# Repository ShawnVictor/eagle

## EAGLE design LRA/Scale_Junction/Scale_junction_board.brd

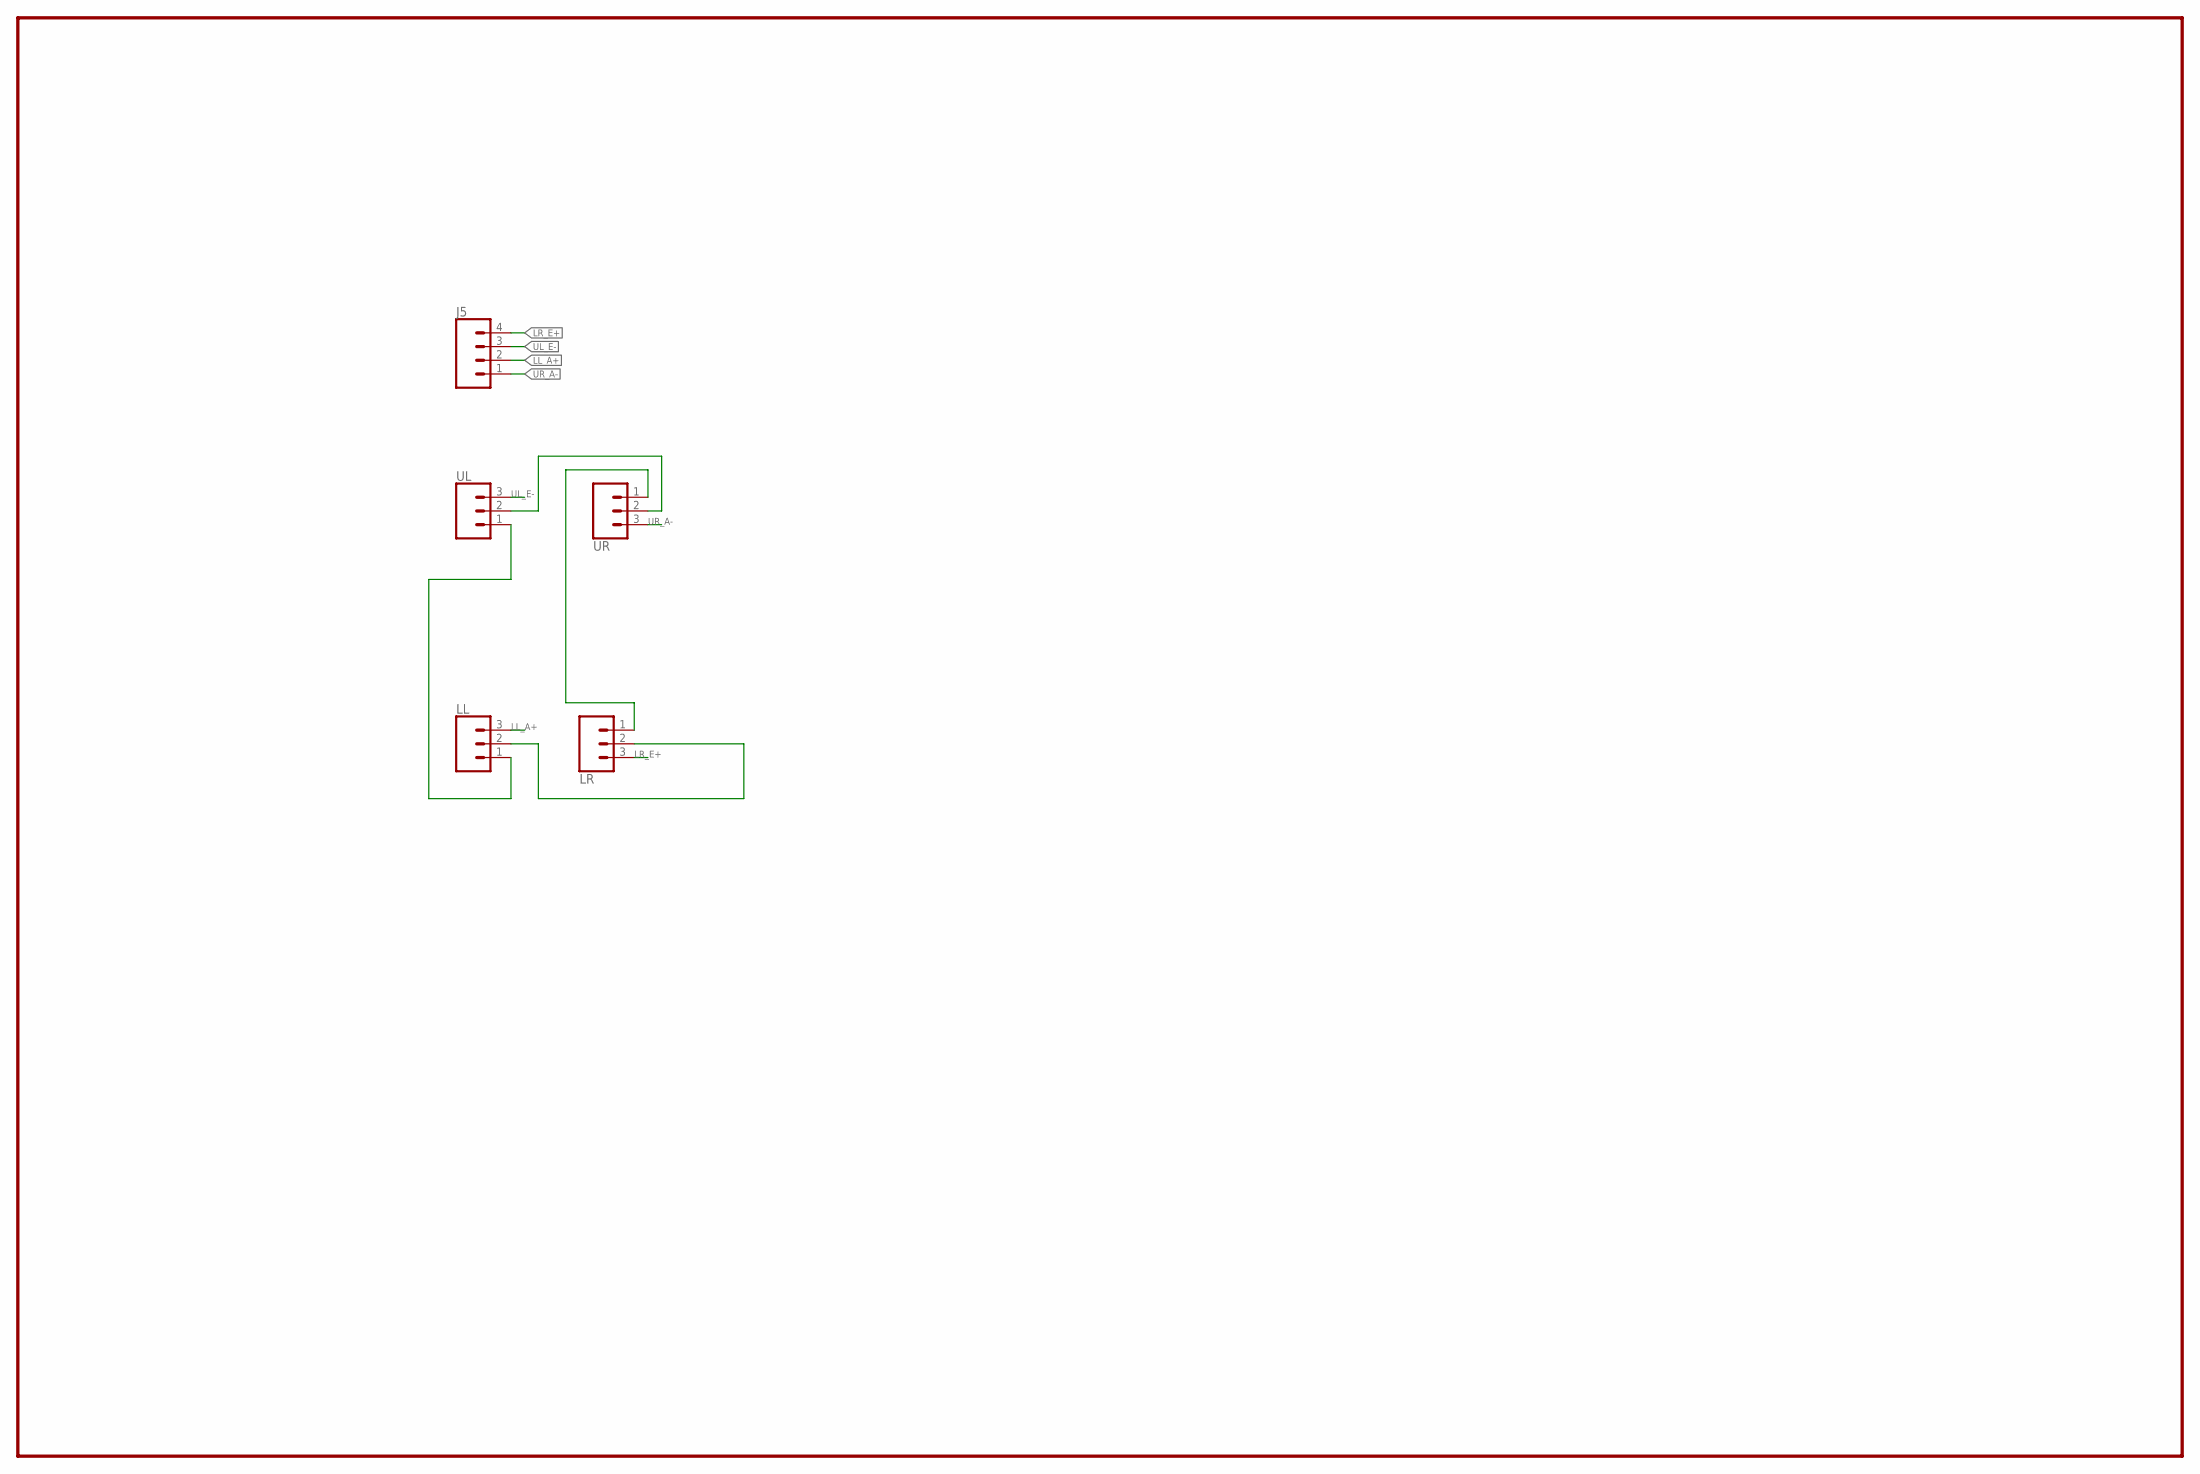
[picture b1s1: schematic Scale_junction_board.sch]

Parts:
J5: CONN_04LONGPADS; 1X04_LONGPADS
LL: CONN_03LONGPADS; 1X03_LONGPADS
LR: CONN_03LONGPADS; 1X03_LONGPADS
UL: CONN_03LONGPADS; 1X03_LONGPADS
UR: CONN_03LONGPADS; 1X03_LONGPADS

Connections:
LL_A+: J5.2, LL.3
LR_E+: J5.4, LR.3
unnamed: LL.1, UL.1
unnamed: LR.1, UR.1
unnamed: UL.2, UR.2
unnamed: LL.2, LR.2
UL_E-: J5.3, UL.3
UR_A-: J5.1, UR.3

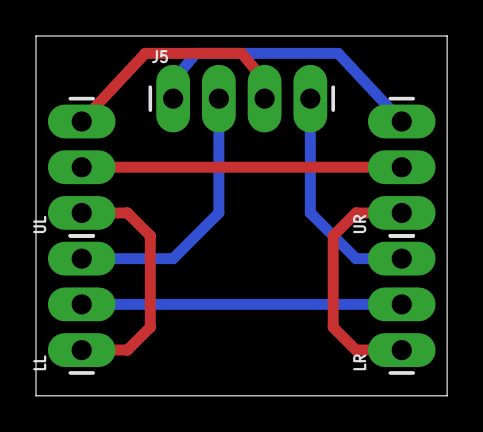
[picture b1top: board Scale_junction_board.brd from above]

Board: 2 copper layers, 22.8 x 20.0 mm, 5 parts (0 on the bottom side), 8 nets.

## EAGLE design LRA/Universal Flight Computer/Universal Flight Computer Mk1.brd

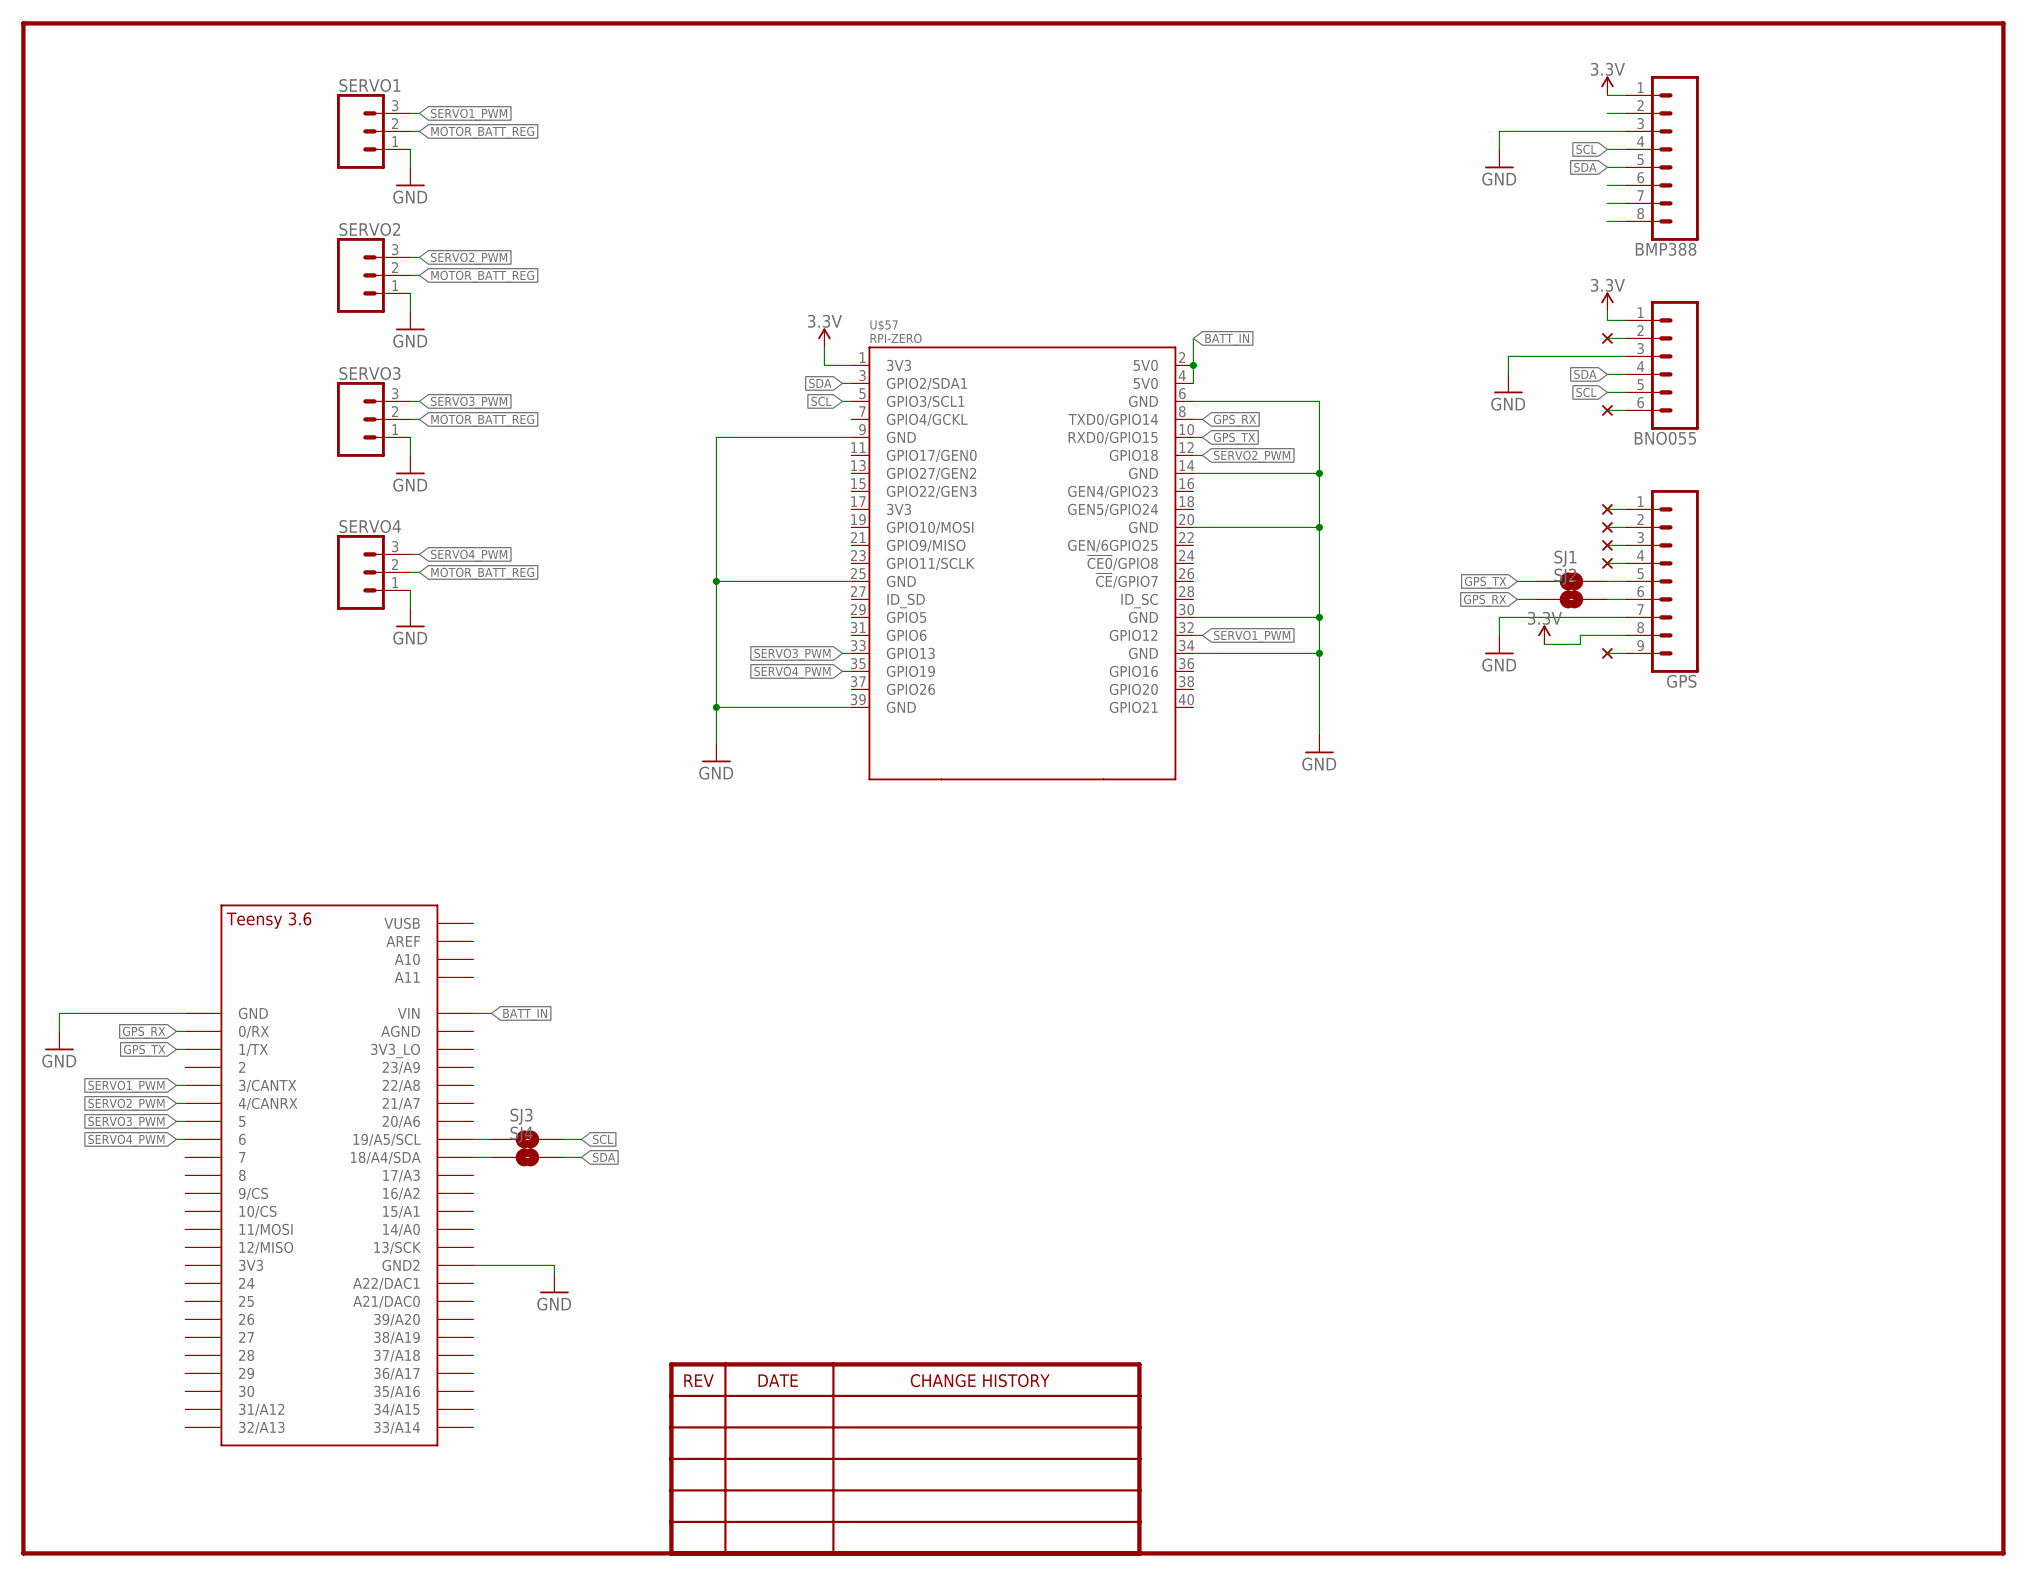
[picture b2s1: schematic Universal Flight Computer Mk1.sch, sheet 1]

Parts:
BMP388: CONN_08"; 1X08
BNO055: CONN_06SILK_FEMALE_PTH; 1X06
GPS: CONN_09; 1X09
SERVO1, SERVO2, SERVO3, SERVO4: CONN_03; 1X03
SJ1, SJ2, SJ3, SJ4: SOLDERJUMPERNO; SJ_2S-NO
U$5, U$6, U$7, U$8, U$9, U$10, U$11: NC
U$12: TEENSY_3.5/3.6_BASIC
U$57: RPI-ZERO; RASPBERRYPI_BASTELSTUBE_V13_RASPI_BOARD_B+_FULL

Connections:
3.3V: BMP388.1, BNO055.1, GPS.8, U$57.1 (3V3)
BATT_IN: U$12.VIN, U$57.2 (5V0), U$57.4 (5V0); also elsewhere on the board
BMP_CS: BMP388.7
BMP_INT: BMP388.8
BMP_SDI: BMP388.6
GND: BMP388.3, BNO055.3, GPS.7, SERVO1.1, SERVO2.1, SERVO3.1, SERVO4.1, U$12.GND, U$12.GND2, U$57.6 (GND), U$57.9 (GND), U$57.14 (GND), U$57.20 (GND), U$57.25 (GND), U$57.30 (GND), U$57.34 (GND), U$57.39 (GND); also elsewhere on the board
GPS_RX: GPS.6, SJ2.1, SJ2.2, U$12.0/RX, U$57.8 (TXD0/GPIO14)
GPS_TX: GPS.5, SJ1.1, SJ1.2, U$12.1/TX, U$57.10 (RXD0/GPIO15)
MOTOR_BATT_REG: SERVO1.2, SERVO2.2, SERVO3.2, SERVO4.2; also elsewhere on the board
unnamed: SJ3.1, U$12.19/A5/SCL
unnamed: SJ4.1, U$12.18/A4/SDA
SCL: BMP388.4, BNO055.5, SJ3.2, U$57.5 (GPIO3/SCL1)
SDA: BMP388.5, BNO055.4, SJ4.2, U$57.3 (GPIO2/SDA1)
SERVO1_PWM: SERVO1.3, U$12.3/CANTX, U$57.32 (GPIO12)
SERVO2_PWM: SERVO2.3, U$12.4/CANRX, U$57.12 (GPIO18)
SERVO3_PWM: SERVO3.3, U$12.5, U$57.33 (GPIO13)
SERVO4_PWM: SERVO4.3, U$12.6, U$57.35 (GPIO19)

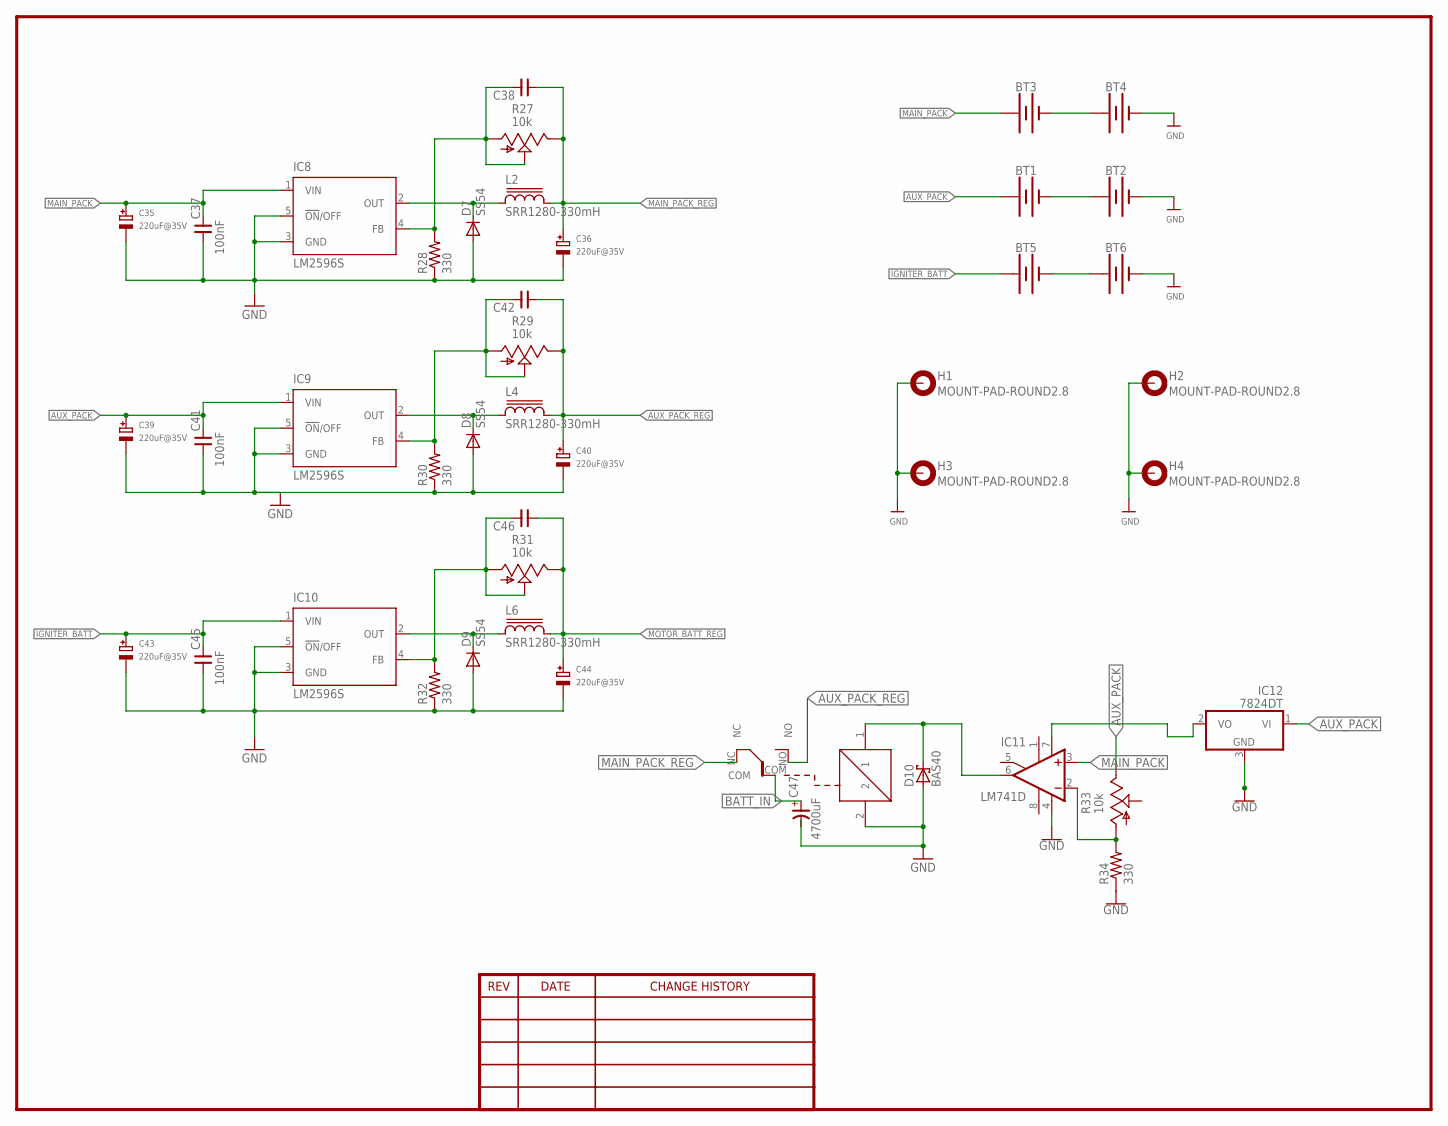
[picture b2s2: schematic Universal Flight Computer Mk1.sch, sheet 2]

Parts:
BT1, BT2, BT3, BT4, BT5, BT6: BATTERY-18650; BATTERY_18650-HOLDER
C35, C36, C39, C40, C43, C44: 220uF@35V; PANASONIC_D
C37, C41, C45: 100nF; 0603
C38, C42, C46: CNP-0603; 0603
C47: 4700uF; E-025X065
D7, D8, D9: SS54; DO214AB
D10: BAS40; SOT23
H1, H2, H3, H4: MOUNT-PAD-ROUND2.8; 2,8-PAD
IC8, IC9, IC10: LM2596S; TO263-5
IC11: LM741D; SO08
IC12: 7824DT; TO252
L2, L4, L6: SRR1280-330mH; SRR1280
R27, R29, R31, R33: 10k; S64W
R28, R30, R32, R34: 330; R0603
U$54: RW-SH

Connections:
AUX_PACK: BT1.PWR@1 (+), C39.+, C41.2, IC9.1 (VIN), IC12.1 (VI), R33.E
AUX_PACK_REG: C40.+, C42.1, L4.2, R29.E, U$54.NO
BATT_IN: C47.+, D10.3 (C), IC11.6 (OUT), U$54.1, U$54.COM; also elsewhere on the board
GND: BT2.GND@1 (-), BT4.GND@1 (-), BT6.GND@1 (-), C39.-, C40.-, C41.1, C43.-, C44.-, C45.1, D8.A, D9.A, D10.1 (A), H1.B2,8, H2.B2,8, H3.B2,8, H4.B2,8, IC9.3 (GND), IC9.5 (!ON!/OFF), IC10.3 (GND), IC10.5 (!ON!/OFF), IC11.4 (V-), IC12.3 (GND), R30.1, R32.1, R34.1, U$54.2; also elsewhere on the board
IGNITER_BATT: BT5.PWR@1 (+), C43.+, C45.2, IC10.1 (VIN)
MAIN_PACK: BT3.PWR@1 (+), C35.+, C35.-, C36.-, C37.1, C37.2, D7.A, IC8.1 (VIN), IC8.3 (GND), IC8.5 (!ON!/OFF), IC11.3 (+IN), R28.1
MAIN_PACK_REG: C36.+, C38.1, L2.2, R27.E, U$54.NC
MOTOR_BATT_REG: C44.+, C46.1, L6.2, R31.E; also elsewhere on the board
unnamed: BT3.GND@1 (-), BT4.PWR@1 (+)
unnamed: BT1.GND@1 (-), BT2.PWR@1 (+)
unnamed: D7.C, IC8.2 (OUT), L2.1
unnamed: C38.2, IC8.4 (FB), R27.A, R27.S, R28.2
unnamed: D8.C, IC9.2 (OUT), L4.1
unnamed: C42.2, IC9.4 (FB), R29.A, R29.S, R30.2
unnamed: D9.C, IC10.2 (OUT), L6.1
unnamed: C46.2, IC10.4 (FB), R31.A, R31.S, R32.2
unnamed: IC11.2 (-IN), R33.A, R34.2
unnamed: IC11.7 (V+), IC12.2 (VO)
unnamed: BT5.GND@1 (-), BT6.PWR@1 (+)

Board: 4 copper layers, 64 parts (18 on the bottom side), 30 nets, no tracks yet.

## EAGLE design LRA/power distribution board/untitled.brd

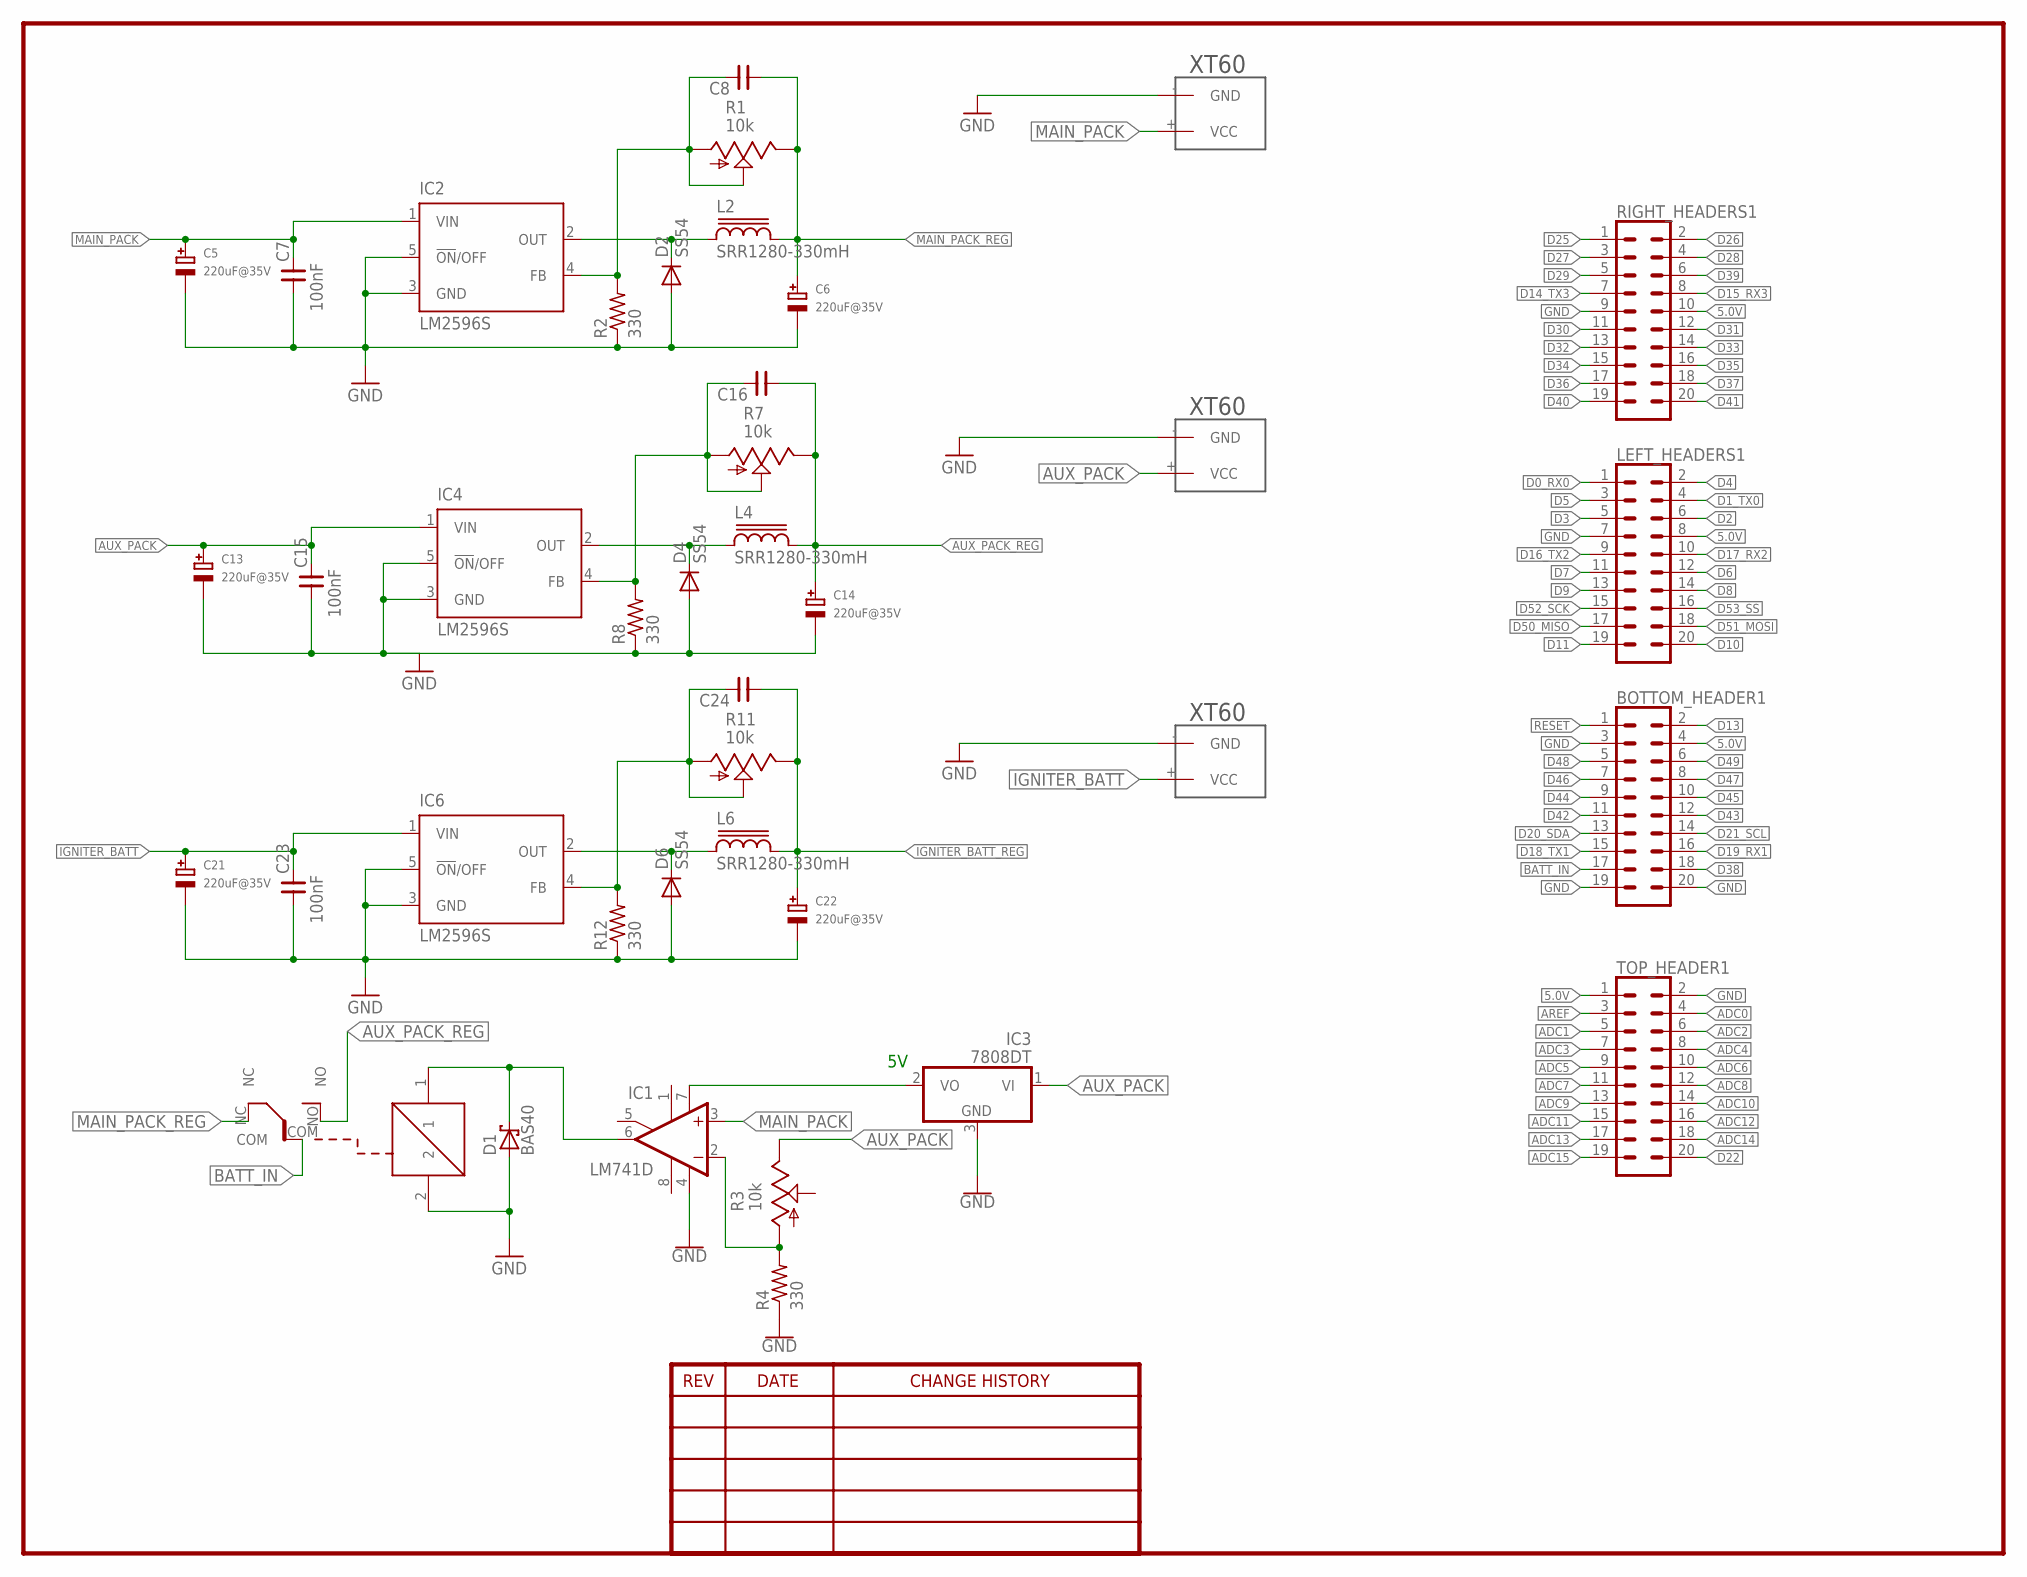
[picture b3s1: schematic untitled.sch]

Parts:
BOTTOM_HEADER1: CONN_10X2; 2X10
C5, C6, C13, C14, C21, C22: 220uF@35V; PANASONIC_D
C7, C15, C23: 100nF; 0603
C8, C16, C24: CNP-0603; 0603
D1: BAS40; SOT23
D2, D4, D6: SS54; DO214AB
IC1: LM741D; SO08
IC2, IC4, IC6: LM2596S; TO263-5
IC3: 7808DT; TO252
L2, L4, L6: SRR1280-330mH; SRR1280
LEFT_HEADERS1: CONN_10X2; 2X10
R1, R3, R7, R11: 10k; S64W
R2, R4, R8, R12: 330; R0603
RIGHT_HEADERS1: CONN_10X2; 2X10
TOP_HEADER1: CONN_10X2; 2X10
U$1, U$2, U$3: XT60
U$9: RW-SH

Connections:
5.0V: BOTTOM_HEADER1.4, LEFT_HEADERS1.8, RIGHT_HEADERS1.10, TOP_HEADER1.1
ADC0: TOP_HEADER1.4
ADC1: TOP_HEADER1.5
ADC2: TOP_HEADER1.6
ADC3: TOP_HEADER1.7
ADC4: TOP_HEADER1.8
ADC5: TOP_HEADER1.9
ADC6: TOP_HEADER1.10
ADC7: TOP_HEADER1.11
ADC8: TOP_HEADER1.12
ADC9: TOP_HEADER1.13
ADC10: TOP_HEADER1.14
ADC11: TOP_HEADER1.15
ADC12: TOP_HEADER1.16
ADC13: TOP_HEADER1.17
ADC14: TOP_HEADER1.18
ADC15: TOP_HEADER1.19
AREF: TOP_HEADER1.3
AUX_PACK: C13.+, C15.2, IC3.1 (VI), IC4.1 (VIN), R3.E, U$2.+ (VCC)
AUX_PACK_REG: C14.+, C16.1, L4.2, R7.E, U$9.NO
BATT_IN: BOTTOM_HEADER1.17, D1.3 (C), IC1.6 (OUT), U$9.1, U$9.COM
D0_RX0: LEFT_HEADERS1.1
D1_TX0: LEFT_HEADERS1.4
D2: LEFT_HEADERS1.6
D3: LEFT_HEADERS1.5
D4: LEFT_HEADERS1.2
D5: LEFT_HEADERS1.3
D6: LEFT_HEADERS1.12
D7: LEFT_HEADERS1.11
D8: LEFT_HEADERS1.14
D9: LEFT_HEADERS1.13
D10: LEFT_HEADERS1.20
D11: LEFT_HEADERS1.19
D13: BOTTOM_HEADER1.2
D14_TX3: RIGHT_HEADERS1.7
D15_RX3: RIGHT_HEADERS1.8
D16_TX2: LEFT_HEADERS1.9
D17_RX2: LEFT_HEADERS1.10
D18_TX1: BOTTOM_HEADER1.15
D19_RX1: BOTTOM_HEADER1.16
D20_SDA: BOTTOM_HEADER1.13
D21_SCL: BOTTOM_HEADER1.14
D22: TOP_HEADER1.20
D25: RIGHT_HEADERS1.1
D26: RIGHT_HEADERS1.2
D27: RIGHT_HEADERS1.3
D28: RIGHT_HEADERS1.4
D29: RIGHT_HEADERS1.5
D30: RIGHT_HEADERS1.11
D31: RIGHT_HEADERS1.12
D32: RIGHT_HEADERS1.13
D33: RIGHT_HEADERS1.14
D34: RIGHT_HEADERS1.15
D35: RIGHT_HEADERS1.16
D36: RIGHT_HEADERS1.17
D37: RIGHT_HEADERS1.18
D38: BOTTOM_HEADER1.18
D39: RIGHT_HEADERS1.6
D40: RIGHT_HEADERS1.19
D41: RIGHT_HEADERS1.20
D42: BOTTOM_HEADER1.11
D43: BOTTOM_HEADER1.12
D44: BOTTOM_HEADER1.9
D45: BOTTOM_HEADER1.10
D46: BOTTOM_HEADER1.7
D47: BOTTOM_HEADER1.8
D48: BOTTOM_HEADER1.5
D49: BOTTOM_HEADER1.6
D50_MISO: LEFT_HEADERS1.17
D51_MOSI: LEFT_HEADERS1.18
D52_SCK: LEFT_HEADERS1.15
D53_SS: LEFT_HEADERS1.16
GND: BOTTOM_HEADER1.3, BOTTOM_HEADER1.19, BOTTOM_HEADER1.20, C13.-, C14.-, C15.1, C21.-, C22.-, C23.1, D1.1 (A), D4.A, D6.A, IC1.4 (V-), IC3.3 (GND), IC4.3 (GND), IC4.5 (!ON!/OFF), IC6.3 (GND), IC6.5 (!ON!/OFF), LEFT_HEADERS1.7, R4.1, R8.1, R12.1, RIGHT_HEADERS1.9, TOP_HEADER1.2, U$1.- (GND), U$2.- (GND), U$3.- (GND), U$9.2
IGNITER_BATT: C21.+, C23.2, IC6.1 (VIN), U$3.+ (VCC)
IGNITER_BATT_REG: C22.+, C24.1, L6.2, R11.E
MAIN_PACK: C5.+, C5.-, C6.-, C7.1, C7.2, D2.A, IC1.3 (+IN), IC2.1 (VIN), IC2.3 (GND), IC2.5 (!ON!/OFF), R2.1, U$1.+ (VCC)
MAIN_PACK_REG: C6.+, C8.1, L2.2, R1.E, U$9.NC
unnamed: D2.C, IC2.2 (OUT), L2.1
unnamed: C8.2, IC2.4 (FB), R1.A, R1.S, R2.2
unnamed: IC1.2 (-IN), R3.A, R4.2
unnamed: D4.C, IC4.2 (OUT), L4.1
unnamed: C16.2, IC4.4 (FB), R7.A, R7.S, R8.2
unnamed: IC1.7 (V+), IC3.2 (VO)
unnamed: D6.C, IC6.2 (OUT), L6.1
unnamed: C24.2, IC6.4 (FB), R11.A, R11.S, R12.2
RESET: BOTTOM_HEADER1.1

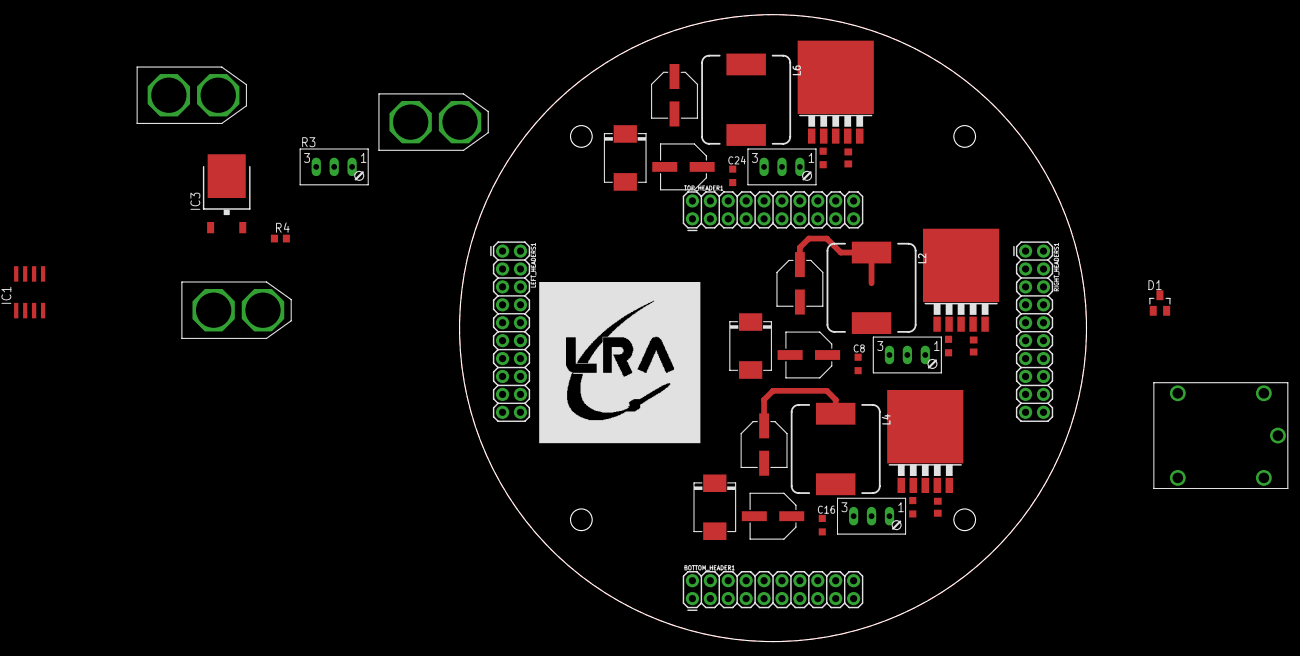
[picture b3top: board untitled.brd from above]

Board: 2 copper layers, 88.9 x 88.9 mm, 40 parts (0 on the bottom side), 17 nets.

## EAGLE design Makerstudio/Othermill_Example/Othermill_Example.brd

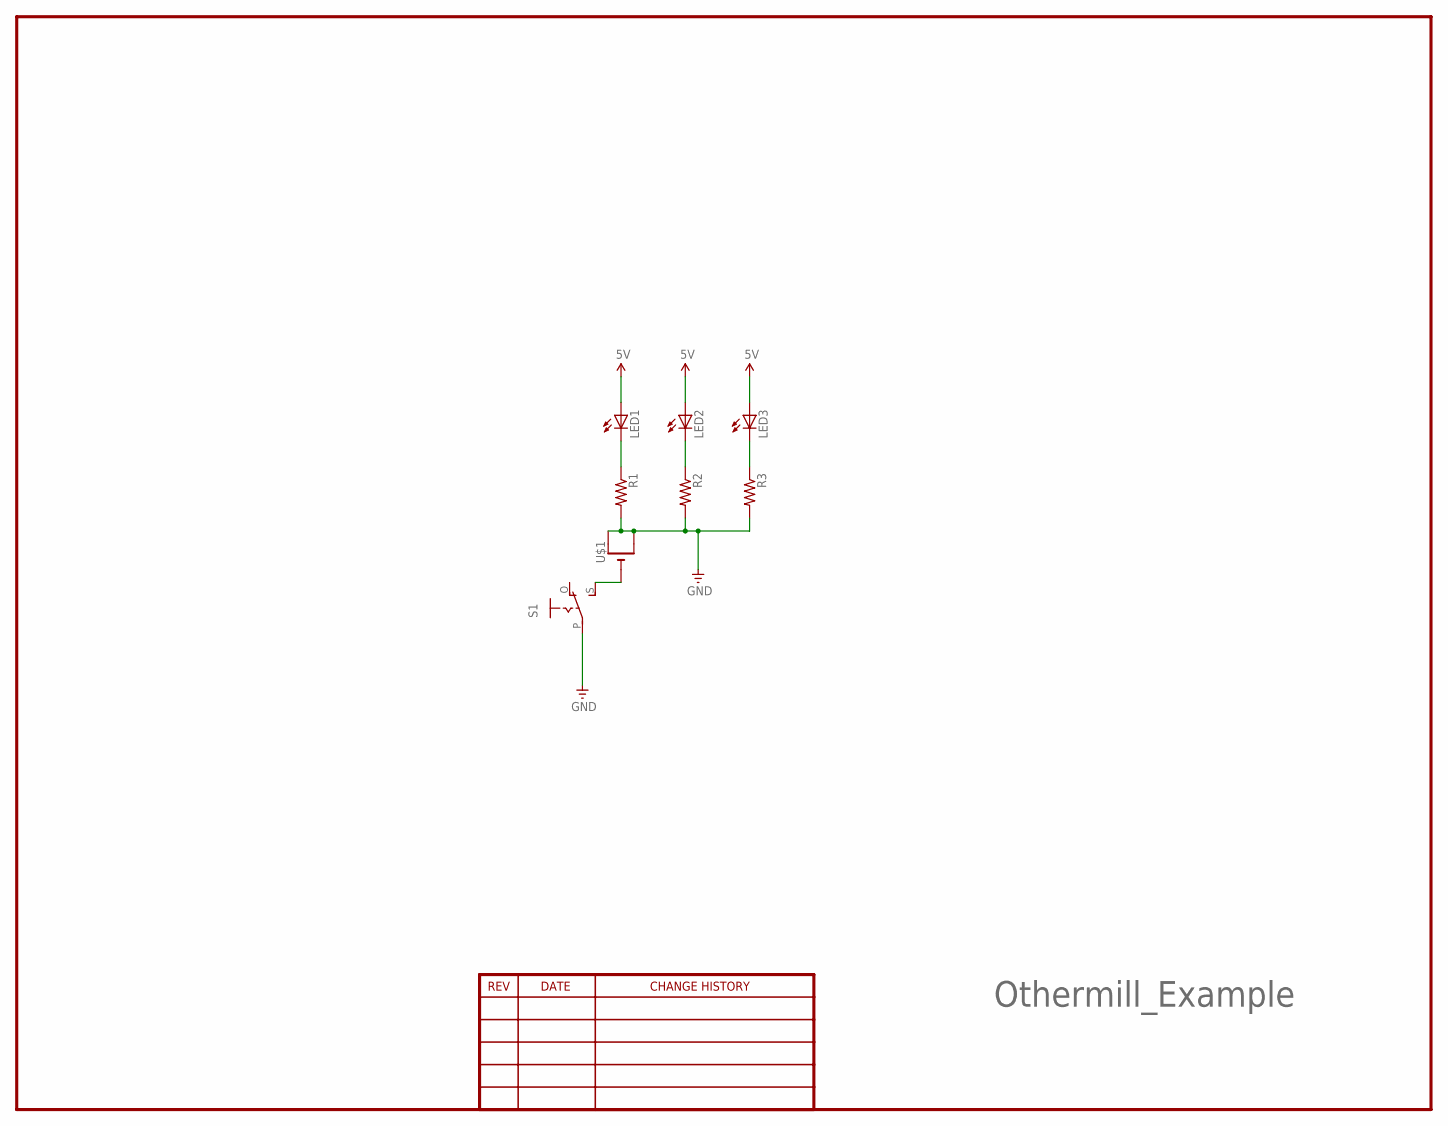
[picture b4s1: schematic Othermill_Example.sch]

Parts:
LED1, LED2, LED3: LED5MM
R1, R2, R3: R-US_0207/7; 0207/7
S1: EG1218S; EG1218
U$1: CR1220SMT; CR1220-SMD

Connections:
5V: LED1.A, LED2.A, LED3.A
GND: R1.2, R2.2, R3.2, S1.P, U$1.+$1 (+), U$1.+$2 (+1)
unnamed: LED1.K (C), R1.1
unnamed: LED2.K (C), R2.1
unnamed: LED3.K (C), R3.1
unnamed: S1.S, U$1.-

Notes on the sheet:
Othermill_Example

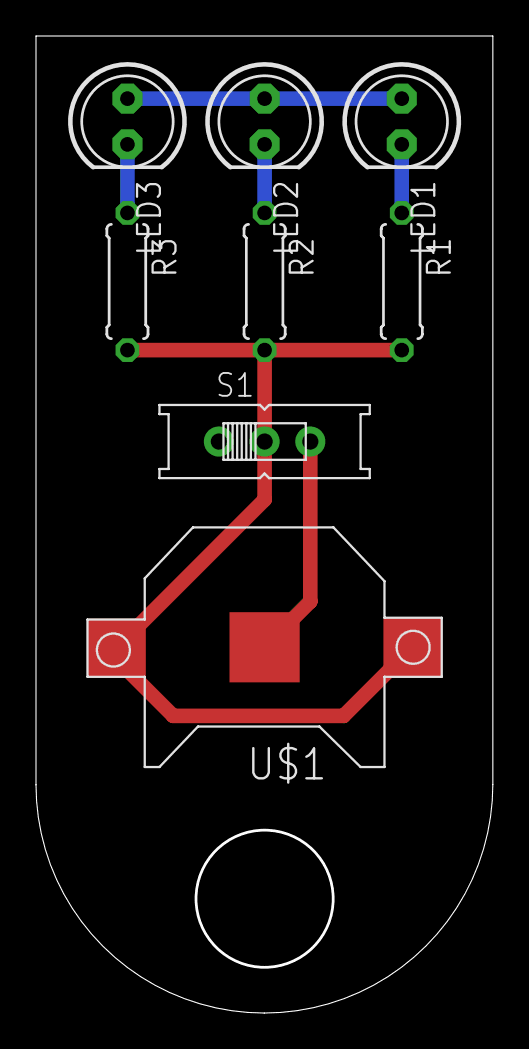
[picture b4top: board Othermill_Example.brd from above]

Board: 2 copper layers, 25.4 x 54.3 mm, 8 parts (0 on the bottom side), 6 nets.

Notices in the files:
parts and their libraries:
SparkFun-Connectors: Licensing: Creative Commons ShareAlike 4.0 International - https://creativecommons.org/licenses/by-sa/4.0
dframes: Copyright (C) 2004, Bob Starr (bobstarr@mindspring.com)
inductor-bourns: Copyright (C) 2008, Bob Starr
